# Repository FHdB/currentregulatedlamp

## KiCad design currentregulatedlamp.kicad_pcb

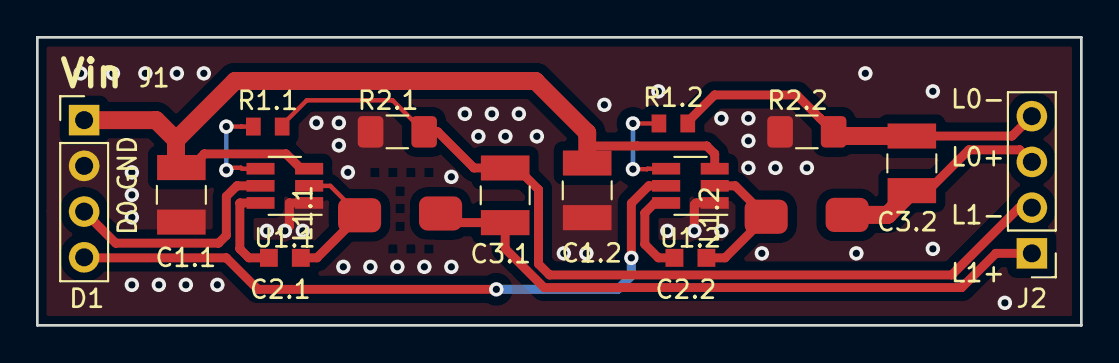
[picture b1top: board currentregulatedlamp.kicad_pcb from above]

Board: 2 copper layers, 58.0 x 16.0 mm, 16 parts (0 on the bottom side), 14 nets.

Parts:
C1.1, C1.2, C3.1, C3.2: 10u/25V; C_1210_3225Metric_Pad1.39x2.70mm_HandSolder
C2.1, C2.2: 100n/50V; C_0603_1608Metric_Pad0.99x1.00mm_HandSolder
J1, J2: Conn_01x04; PinHeader_1x04_P2.54mm_Vertical
L1.1, L1.2: L; L_Wuerth_WE-PD-6050
R1.1, R1.2: 1k/5%; R_0603_1608Metric
R2.1, R2.2: R; R_1206_3216Metric_Pad1.42x1.75mm_HandSolder
U1.1, U1.2: TPS54200DDC; SOT-23-6_Handsoldering

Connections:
+24V: C1.1.1, C1.2.1, J1.1, U1.1.3, U1.2.3
/DIM: J1.3, U1.1.5
/DIM_1: J1.4, U1.2.5
/LED+: C3.1.1, J2.1, L1.1.2
/LED+_1: C3.2.1, J2.3, L1.2.2
/LED-: C3.1.2, J2.2, R1.1.2, R2.1.1
/LED-_1: C3.2.2, J2.4, R1.2.2, R2.2.1
/LED_2/BOOT: C2.2.1, U1.2.6
/LED_2/FB: R1.2.1, U1.2.4
/LED_2/SW: C2.2.2, L1.2.1, U1.2.2
/TPS54200/BOOT: C2.1.1, U1.1.6
/TPS54200/FB: R1.1.1, U1.1.4
/TPS54200/SW: C2.1.2, L1.1.1, U1.1.2
GND: C1.1.2, C1.2.2, J1.2, R2.1.2, R2.2.2, U1.1.1, U1.2.1

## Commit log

2019-02-02 include libraries
    added project specific libraries that allow porting the design
2019-03-03 Schematic replication
    decided on path for replicating current regulator
2019-05-18 added some values
    added component values to step down converter circuit
2019-05-19 PCB ready for first test run
    reduced number of channels to 2 for first prototype
2019-05-22 silkscreen bottom layer
    added KiCAD and OSHW logo to bottom
2019-06-04 Added values
    Added component values for easier part ordering
